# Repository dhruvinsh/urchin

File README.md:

# Ursa - Urchin on Steroids

<span>

</span>

I created this design because I like the [Urchin](https://github.com/duckyb/urchin) and wanted to try something with 34 keys.  
**This is a strictly wireless-only design, and is only compatible with ZMK / nice!nano. Only Cherry MX switches + Hotswap are suported!**

> Q: Why is this not just another one?  
*A: Original Urchin is based of choc switch. They are good but I still wanted to try something with MX keycaps. Hence we are here looking at the new keeyboard Ursa.*

**If you enjoy my work, please consider ⭐ starring and/or ❤ sponsoring it.**

## Features
- [x] Design fully optimized for wireless    
- [x] Native nice!view support  
- [x] Familiar Ferris/Sweep/Urchin layout  
- [x] Improved outline shape  
- [x] Support for Cherry MX Socket
- [x] Remove diode footprint from the top surface

### Upcoming
- [ ] Mounting points for cases
- [ ] Plate file
- [ ] MCU Cover file
- [ ] Tray case 3D model

## Part list (for both sides)
#### Required
- 1× PCB Kit (files for it are in [releases](https://github.com/duckyb/urchin/releases))
- 34× Kailh **MX** Hotswap Sockets
- 34× MX Compatible switches
- 34× Keycaps
- 34× SMD diodes (SOD-123)
- 2× nice!nano
- 2× Lipo battery (301230)
- 48× mill-max machined pins
- 2× Pair of female headers
#### Optional
- 2× nice!view
- 2× Reset switch (B3U-1000P(M))
- 2× Power switch (MSK 12C02)
- 10× adhesive silicone feet

## Reference build guide:

## Firmware
Coming soon but for now you can refere to below,

> Urchin supports ZMK only. To get started with ZMK visit the [zmk-urchin repository](https://github.com/duckyb/zmk-urchin) and follow the provided instructions.

## Credits
- Urchin by [duckyb](https://github.com/duckyb/urchin)

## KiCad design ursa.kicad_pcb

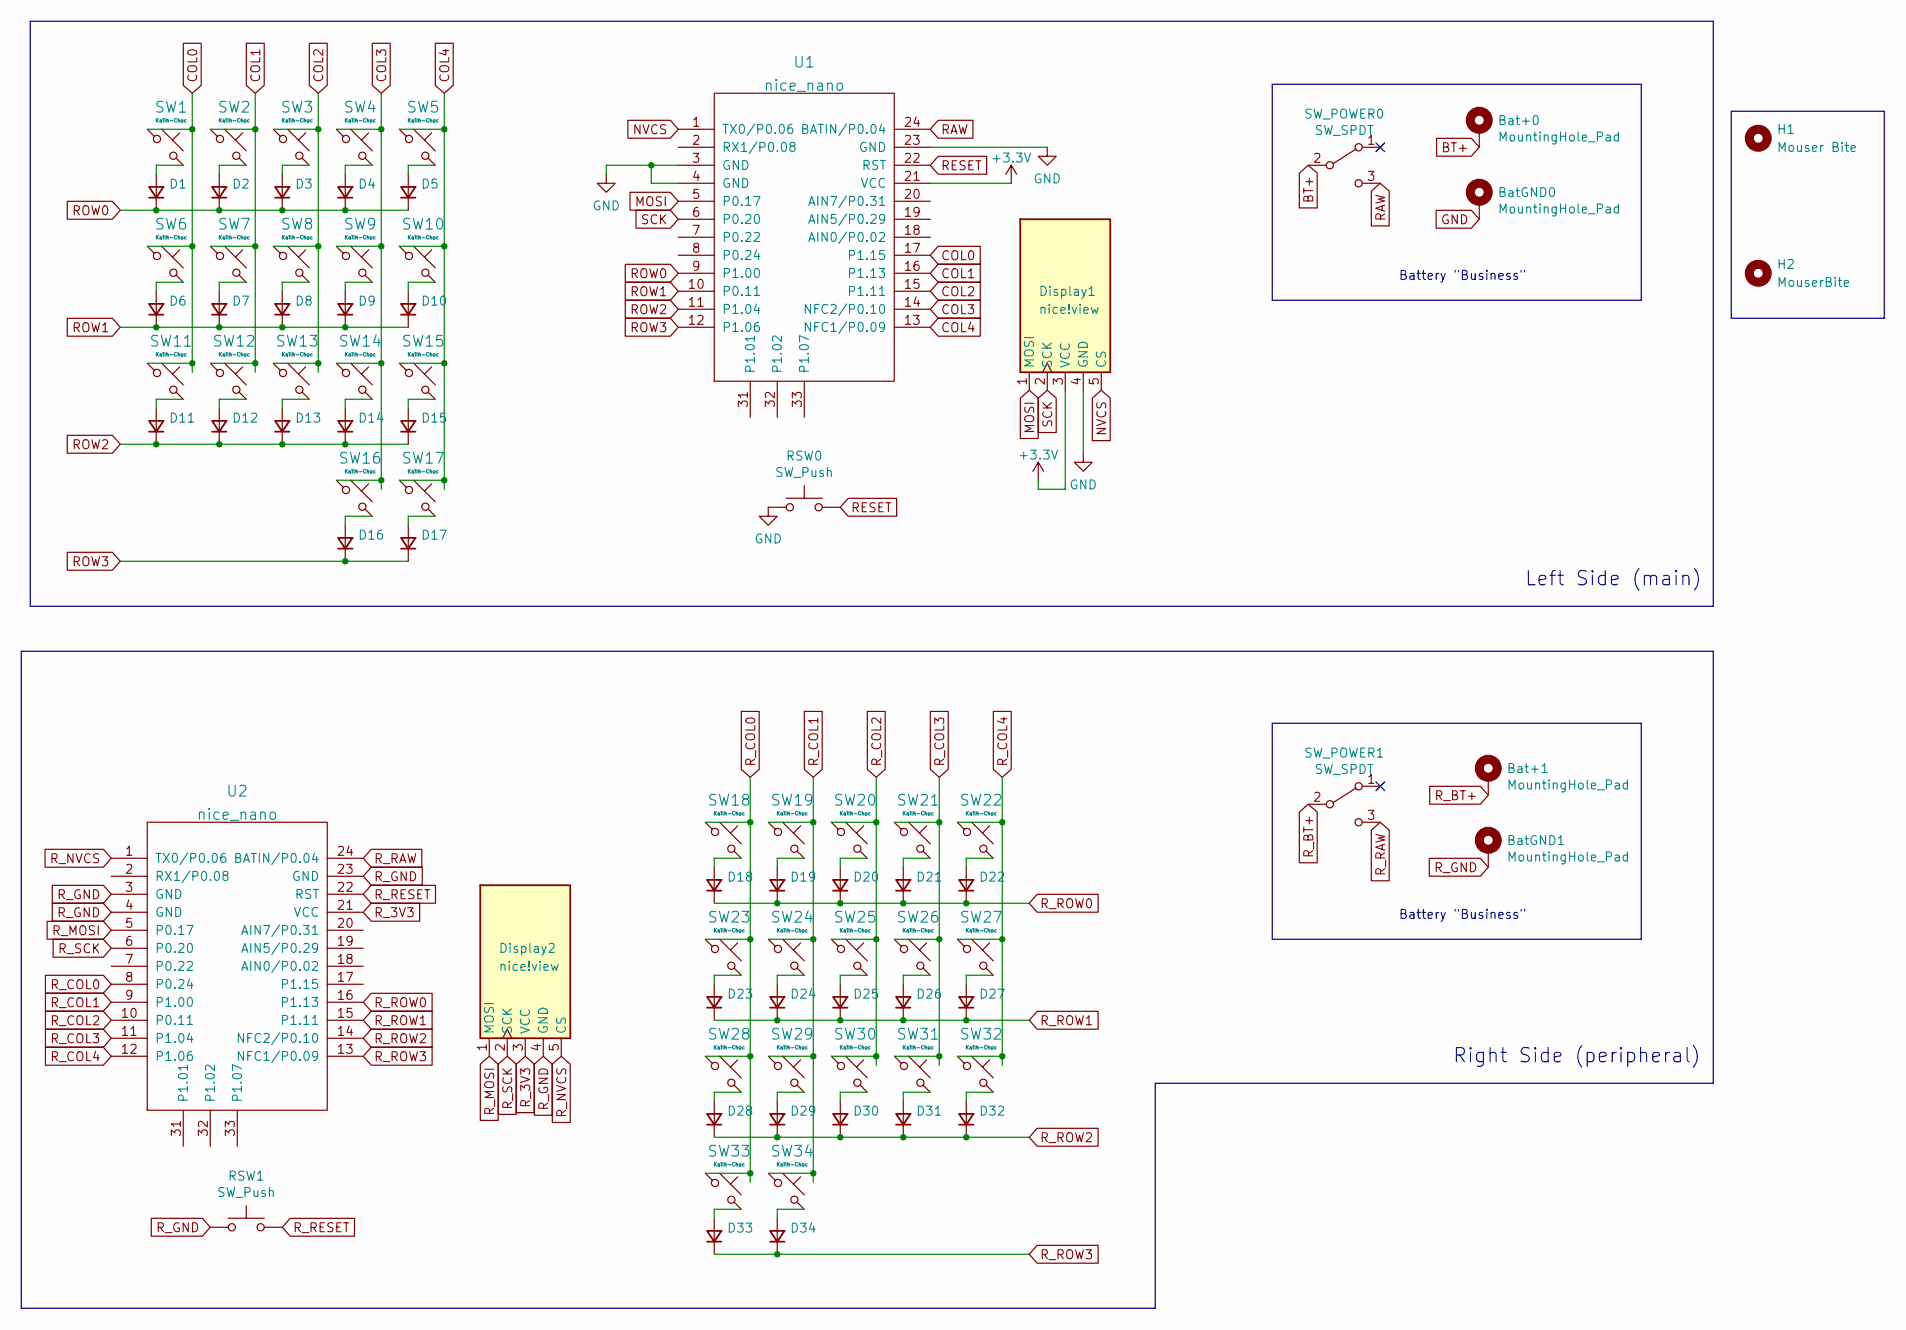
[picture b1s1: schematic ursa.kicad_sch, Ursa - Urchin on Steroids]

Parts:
Bat+0, Bat+1: MountingHole_Pad; 1pin_conn
BatGND0, BatGND1: MountingHole_Pad; 1pin_conn
D1, D2, D3, D4, D5, D6, D7, D8, D9, D10, D11, D12, D13, D14, D15, D16, D17, D18, D19, D20, D21, D22, D23, D24, D25, D26, D27, D28, D29, D30, D31, D32, D33, D34: diode; D_SOD-123
Display1, Display2: nice!view; nice_view
H1: Mouser Bite; mouse-bite-2mm-slot-with-space-for-track
H2: MouserBite; mouse-bite-2mm-slot-with-space-for-track
RSW0, RSW1: SW_Push; SW_RESET
SW1, SW2, SW3, SW4, SW5, SW6, SW7, SW8, SW9, SW10, SW11, SW12, SW13, SW14, SW15, SW16, SW17, SW18, SW19, SW20, SW21, SW22, SW23, SW24, SW25, SW26, SW27, SW28, SW29, SW30, SW31, SW32, SW33, SW34: Kailh-Choc; SW_MX_HS_1u
SW_POWER0, SW_POWER1: SW_SPDT; SW_MSK12C02-HB
U1, U2: nice_nano

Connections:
+3V3: Display1.3 (VCC), U1.21 (VCC)
BT+: Bat+0.1, SW_POWER0.2 (B)
COL0: SW1.1, SW6.1, SW11.1, U1.17 (P1.15)
COL1: SW2.1, SW7.1, SW12.1, U1.16 (P1.13)
COL2: SW3.1, SW8.1, SW13.1, U1.15 (P1.11)
COL3: SW4.1, SW9.1, SW14.1, SW16.1, U1.14 (NFC2/P0.10)
COL4: SW5.1, SW10.1, SW15.1, SW17.1, U1.13 (NFC1/P0.09)
GND: BatGND0.1, Display1.4 (GND), RSW0.1, U1.3 (GND), U1.4 (GND), U1.23 (GND)
MOSI: Display1.1 (MOSI), U1.5 (P0.17)
NVCS: Display1.5 (CS), U1.1 (TX0/P0.06)
unnamed: D1.2 (A), SW1.2
unnamed: D2.2 (A), SW2.2
unnamed: D3.2 (A), SW3.2
unnamed: D4.2 (A), SW4.2
unnamed: D5.2 (A), SW5.2
unnamed: D6.2 (A), SW6.2
unnamed: D7.2 (A), SW7.2
unnamed: D8.2 (A), SW8.2
unnamed: D9.2 (A), SW9.2
unnamed: D10.2 (A), SW10.2
unnamed: D11.2 (A), SW11.2
unnamed: D12.2 (A), SW12.2
unnamed: D13.2 (A), SW13.2
unnamed: D14.2 (A), SW14.2
unnamed: D15.2 (A), SW15.2
unnamed: D16.2 (A), SW16.2
unnamed: D17.2 (A), SW17.2
unnamed: D18.2 (A), SW18.2
unnamed: D19.2 (A), SW19.2
unnamed: D20.2 (A), SW20.2
unnamed: D21.2 (A), SW21.2
unnamed: D22.2 (A), SW22.2
unnamed: D23.2 (A), SW23.2
unnamed: D24.2 (A), SW24.2
unnamed: D25.2 (A), SW25.2
unnamed: D26.2 (A), SW26.2
unnamed: D27.2 (A), SW27.2
unnamed: D28.2 (A), SW28.2
unnamed: D29.2 (A), SW29.2
unnamed: D30.2 (A), SW30.2
unnamed: D31.2 (A), SW31.2
unnamed: D32.2 (A), SW32.2
unnamed: D33.2 (A), SW33.2
unnamed: D34.2 (A), SW34.2
RAW: SW_POWER0.3 (C), U1.24 (BATIN/P0.04)
RESET: RSW0.2, U1.22 (RST)
ROW0: D1.1 (K), D2.1 (K), D3.1 (K), D4.1 (K), D5.1 (K), U1.9 (P1.00)
ROW1: D6.1 (K), D7.1 (K), D8.1 (K), D9.1 (K), D10.1 (K), U1.10 (P0.11)
ROW2: D11.1 (K), D12.1 (K), D13.1 (K), D14.1 (K), D15.1 (K), U1.11 (P1.04)
ROW3: D16.1 (K), D17.1 (K), U1.12 (P1.06)
R_3V3: Display2.3 (VCC), U2.21 (VCC)
R_BT+: Bat+1.1, SW_POWER1.2 (B)
R_COL0: SW18.1, SW23.1, SW28.1, SW33.1, U2.8 (P0.24)
R_COL1: SW19.1, SW24.1, SW29.1, SW34.1, U2.9 (P1.00)
R_COL2: SW20.1, SW25.1, SW30.1, U2.10 (P0.11)
R_COL3: SW21.1, SW26.1, SW31.1, U2.11 (P1.04)
R_COL4: SW22.1, SW27.1, SW32.1, U2.12 (P1.06)
R_GND: BatGND1.1, Display2.4 (GND), RSW1.1, U2.3 (GND), U2.4 (GND), U2.23 (GND)
R_MOSI: Display2.1 (MOSI), U2.5 (P0.17)
R_NVCS: Display2.5 (CS), U2.1 (TX0/P0.06)
R_RAW: SW_POWER1.3 (C), U2.24 (BATIN/P0.04)
R_RESET: RSW1.2, U2.22 (RST)
R_ROW0: D18.1 (K), D19.1 (K), D20.1 (K), D21.1 (K), D22.1 (K), U2.16 (P1.13)
R_ROW1: D23.1 (K), D24.1 (K), D25.1 (K), D26.1 (K), D27.1 (K), U2.15 (P1.11)
R_ROW2: D28.1 (K), D29.1 (K), D30.1 (K), D31.1 (K), D32.1 (K), U2.14 (NFC2/P0.10)
R_ROW3: D33.1 (K), D34.1 (K), U2.13 (NFC1/P0.09)
R_SCK: Display2.2 (SCK), U2.6 (P0.20)
SCK: Display1.2 (SCK), U1.6 (P0.20)

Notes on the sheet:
Right Side (peripheral)
Battery "Business"
Left Side (main)

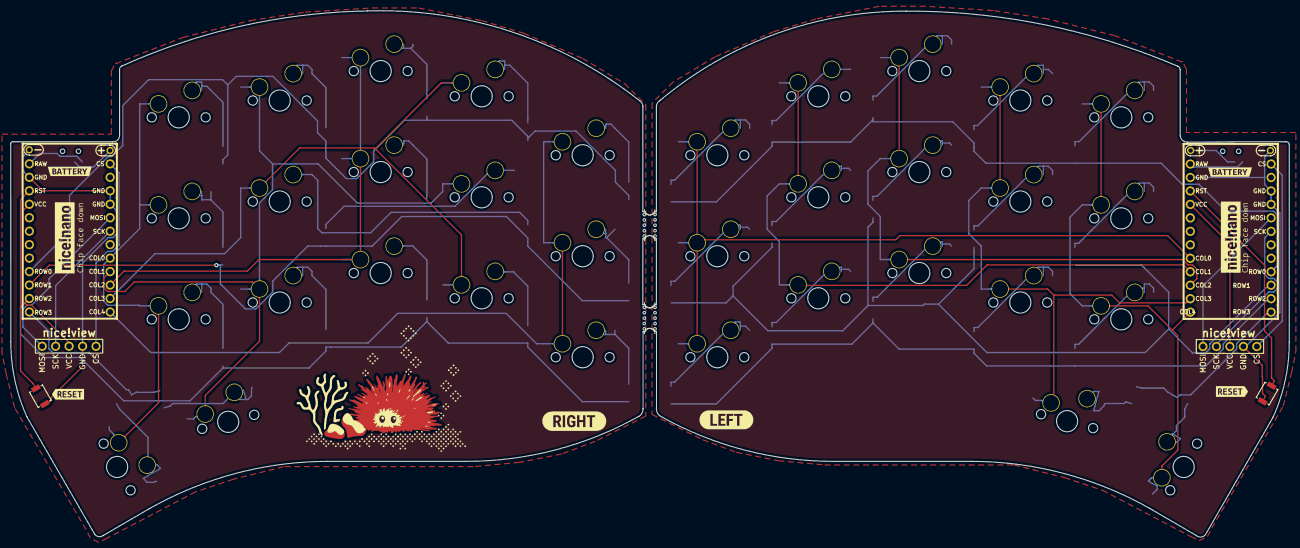
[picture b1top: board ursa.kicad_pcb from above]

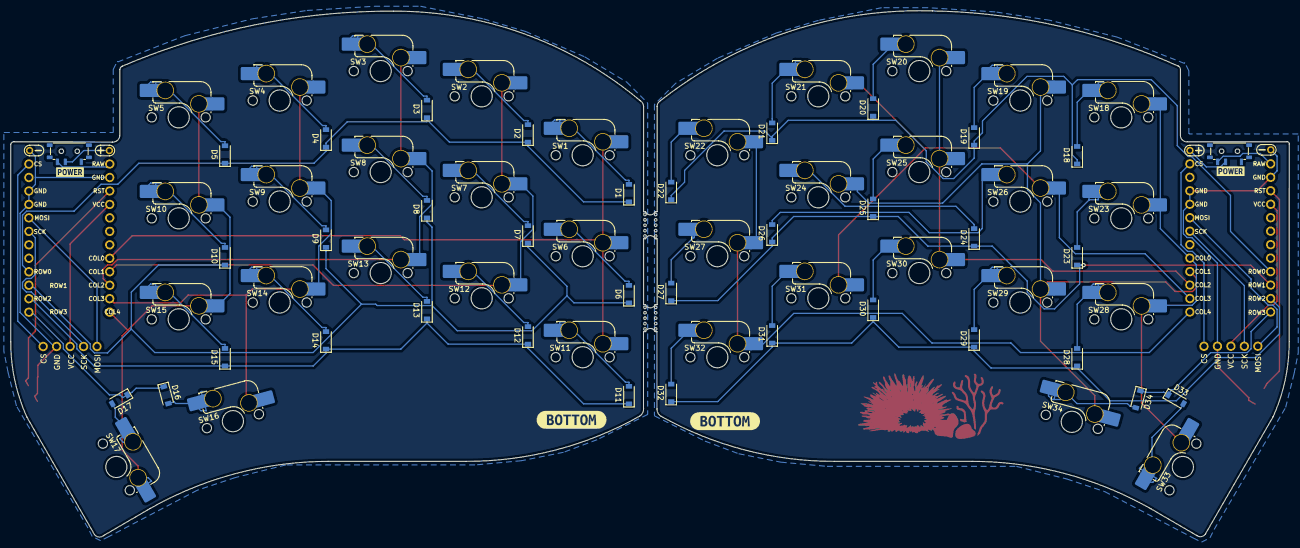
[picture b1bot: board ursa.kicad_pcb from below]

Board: 2 copper layers, 241.2 x 99.3 mm, 99 parts (76 on the bottom side), 68 nets.

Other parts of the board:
1-G***, 3-G***: LOGO
1-kibuzzard-636592CC: G***; kibuzzard-636592CC
2-kibuzzard-6365950B: G***; kibuzzard-6365950B
3-kibuzzard-63658865: G***; kibuzzard-63658865
4-kibuzzard-636588C8: G***; kibuzzard-636588C8
11-kibuzzard-63658823: G***; kibuzzard-63658823
12-kibuzzard-6361375E: G***; kibuzzard-6361375E
13-kibuzzard-63659465: G***; kibuzzard-63659465
kibuzzard-636588C8: G***; kibuzzard-636588C8
kibuzzard-6361375E: G***; kibuzzard-6361375E
kibuzzard-6365884B: G***; kibuzzard-6365884B
kibuzzard-6365951E: G***; kibuzzard-6365951E
kibuzzard-63658830: G***; kibuzzard-63658830
kibuzzard-63659296: G***; kibuzzard-63659296
kibuzzard-63659477: G***; kibuzzard-63659477
logo-3-G***: LOGO

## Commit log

2023-02-08 gitignore update
2023-02-08 try 1: cherry footprint added
    * NOTE: this is not valid implementation. Footprint are fitting that
    does not mean that it will work on physical PCB. Need to redesign it.
2023-02-08 adding some libs
2023-02-09 WIP: cherry mx supported added
    *TODO: routing still missing
2023-02-10 adding random-keyboard-parts
2023-02-10 adding routes and zone
2023-02-10 readme update with images
2023-02-10 minor update to PCB and name changes
2023-02-10 renamed project from urchin to ursa
2023-02-10 mouser bite added as library
2023-02-10 update CI name
2023-02-10 CI: fix config file name
2023-02-10 library changes with new routes
2023-02-11 Update gallery (automated)
2023-02-11 3d file added
2023-02-11 updating readme with new images
